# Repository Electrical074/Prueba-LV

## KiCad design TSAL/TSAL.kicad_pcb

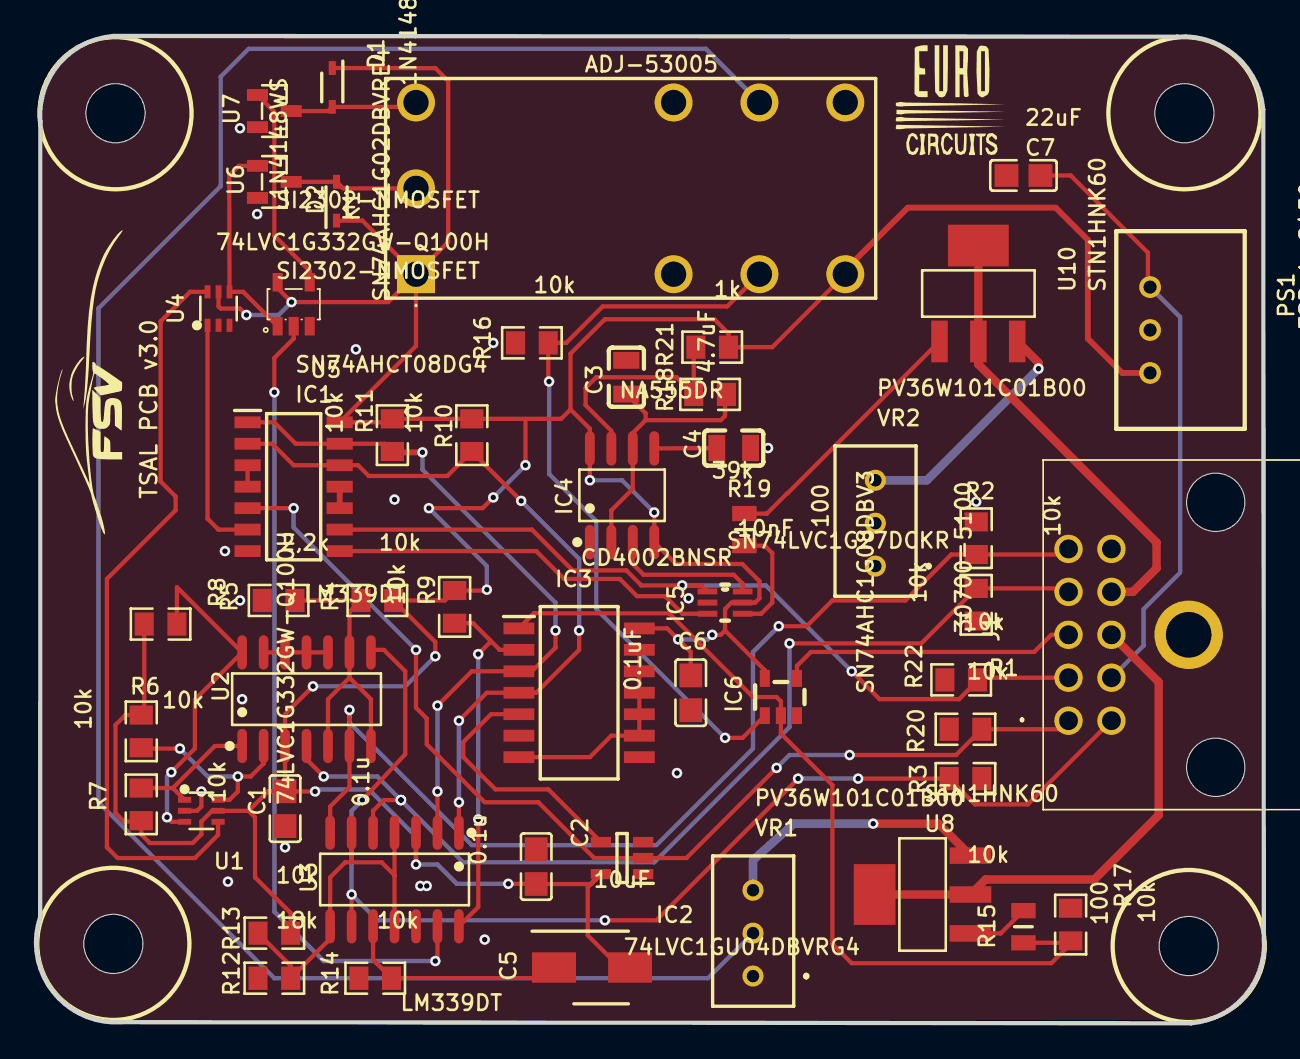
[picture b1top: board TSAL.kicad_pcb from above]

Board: 2 copper layers, 72.7 x 58.4 mm, 55 parts (0 on the bottom side), 43 nets.

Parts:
C1, C2: 0.1u; C0805
C3: 4.7uF; C0805
C4: 10nF; C0805
C5: 10uF; CAPAE430X610N
C6: 0.1uF; C0805
C7: 22uF; C0805
D1, D2: 1N4148WS; SODFL2512X90N
Hole_gge13843: Hole_gge13843
Hole_gge14353: Hole_gge14353
Hole_gge14599: Hole_gge14599
Hole_gge17936: Hole_gge17936
IC1: SN74AHCT08DG4; SOIC127P600X175-14N
IC2: 74LVC1GU04DBVRG4; SOT95P280X145-5N
IC3: CD4002BNSR; SOIC127P780X200-14N
IC4: NA555DR; SOIC-8_L4.9-W3.9-P1.27-LS6.0-BL
IC5: SN74LVC1G27DCKR; SOT65P210X110-6N
IC6: SN74AHC1G08DBV3; SOT-23-5_L2.9-W1.6-P0.95-LS2.8-BR
J1: 30700-5100; 307005100
K1: ADJ-53005; ADJ54005
PS1: TSR_1-2450; TSR-1-24120
R1, R2, R3, R4, R6, R7, R8, R9, R10, R11, R13, R14, R16, R17, R20, R22: 10k; R0805_NEW
R5: 2,2k; R0805_NEW
R12: 18k; R0805_NEW
R15, R19: 100; RESC2012X60N
R18: 39k; R0805_NEW
R21: 1k; R0805_NEW
U1, U4: 74LVC1G332GW-Q100H; SOT-363_L2.0-W1.3-P0.65-LS2.1-BL
U2, U3: LM339DT; SOIC-14_L8.7-W3.9-P1.27-LS6.0-BL
U5: SN74AHC1G02DBVRE4; SOT-23-5_L3.0-W1.7-P0.95-LS2.8-BR
U6, U7: SI2302-NMOSFET; SOT-23-3_L2.9-W1.3-P1.90-LS2.4-BR
U8, U10: STN1HNK60; SOT-223-4_L6.5-W3.5-P2.30-LS7.0-BR
VR1, VR2: PV36W101C01B00; PV36W201C01B00

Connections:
0.9V: R4.1, R5.2, U2.5, U2.7, U2.9
3.2V: R12.2, R13.1, U3.4, U3.6, U3.8, U3.11
+5V: C1.1, C2.1, C5.2, C6.2, D1.1, D2.1, IC1.14, IC2.5, IC3.14, IC4.4, IC4.8, IC5.5, IC6.5, K1.1, K1.4, PS1.3, R4.2, R6.2, R7.2, R8.2, R9.2, R10.2, R11.2, R13.2, R21.2, U1.5, U2.3, U3.3, U4.5, U5.5
ACCU_VOLTAGE_FAULT: IC1.6, U4.1
AIR+: J1.4, R1.2, U2.4, U3.5
AIR+_STATE: IC1.1, IC1.13, IC3.3, R11.1, U3.2
AIR-: J1.5, R2.2, U2.6, U3.7
AIR-_STATE: IC1.2, IC1.12, IC3.4, R10.1, U3.1
DC_LINK_VOLTAGE_FAULT: IC1.8, IC5.3
FAULT_SIGNAL: U4.4, U5.1, U6.1
GND: C1.2, C2.2, C3.1, C4.1, C6.1, C7.1, IC1.7, IC2.3, IC3.7, IC3.9, IC3.10, IC3.11, IC3.12, IC3.13, IC4.1, IC5.2, IC6.3, J1.10, K1.5, PS1.2, R1.1, R2.1, R3.1, R5.1, R12.1, R14.1, R16.1, R17.1, R20.1, R22.1, U1.2, U2.10, U2.11, U2.12, U2.13, U3.12, U4.2, U4.3, U5.3, U6.2, U7.2, VR2.2
G_LED_ACTIVATION: IC3.1, IC6.2, R15.2, R17.2
G_LED_ENABLE: K1.6, VR1.2
IC1_3: IC1.3, IC1.4
IC1_11: IC1.10, IC1.11
IC2_4: IC2.4, IC3.5
IC4_2: C3.2, IC4.2, IC4.6, R18.1
IC4_5: C4.2, IC4.5
IC4_7: IC4.7, R18.2, R21.1
INT_SIGNAL: IC6.1, K1.3, R16.2
K1_8: D1.2, K1.8, U7.3
K1_9: D2.2, K1.9, U6.3
LATCH: U3.13, U5.2
OSCILLATOR: IC4.3, IC5.6
PRECH-RELAY: J1.6, R3.2, U2.8, U3.9
P_RELAY_STATE: IC3.2, R9.1, U3.14
R15_1: R15.1, U8.1
R19_1: R19.1, U10.1
RELAY_FAULT: U1.4, U4.6
R_LED_ACTIVATION: IC5.4, R19.2
TSAL_G_GND: J1.8, U8.2, U8.4
TSAL_R_GND: J1.9, U10.2, U10.4
TS_ACTIVE_ACCU: IC1.5, IC2.2, J1.1, R20.2
TS_ACTIVE_DC_LINK: IC1.9, IC5.1, J1.2, R22.2
TS_STATE: IC6.4, J1.3
U2_1: R7.1, U1.1, U2.1
U2_2: R6.1, U1.6, U2.2
U2_14: R8.1, U1.3, U2.14
U3_10: C5.1, R14.2, U3.10
U5_4: U5.4, U7.1
U8_3: U8.3, VR1.3
U10_3: U10.3, VR2.3
VCC: C7.2, J1.7, PS1.1

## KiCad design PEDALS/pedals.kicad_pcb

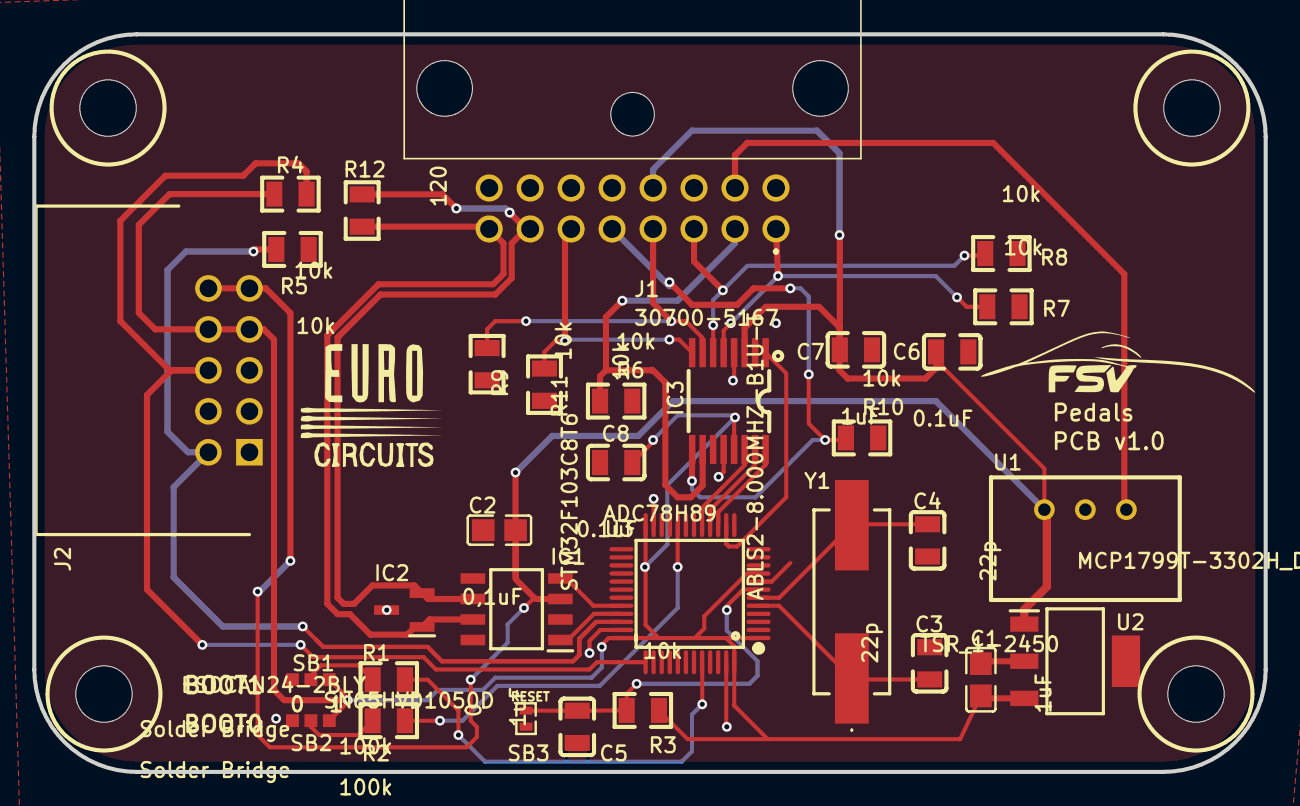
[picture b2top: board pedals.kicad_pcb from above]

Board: 2 copper layers, 76.3 x 45.7 mm, 36 parts (0 on the bottom side), 27 nets.

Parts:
C1, C5, C7: 1uF; C0805
C2: 0,1uF; C0805
C3, C4: 22p; C0805
C6, C8: 0.1uF; C0805
Hole_gge27180: Hole_gge27180
Hole_gge27183: Hole_gge27183
Hole_gge27186: Hole_gge27186
Hole_gge27189: Hole_gge27189
IC1: SN65HVD1050D; SOIC127P600X175-8N
IC2: ESDCAN24-2BLY; SOT105P255X150-3N
IC3: ADC78H89; TSSOP-16_L5.0-W4.4-P0.65-LS6.4-BL
J1: 30700-5167; 307005167
J2: 61201021721; SHDRRA10W64P254X254_2X5_2036X8
R1, R2: 100k; R0805
R3, R4, R5, R6, R7, R8, R9, R10, R11: 10k; R0805
R12: 120; R0805
SB1, SB2: Solder Bridge; SOLDER BRDIGE
SB3: 0; R0402
U1: TSR_1-2450; TSR-1-24120
U2: MCP1799T-3302H_DB; SOT230P700X180-4N
U3: STM32F103C8T6; LQFP-48_L7.0-W7.0-P0.50-LS9.0-BL
Y1: ABLS2-8.000MHZ-B1U-T; ABLS

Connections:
3V3: C1.2, C8.1, IC3.13, J2.7, J2.8, R3.2, R4.2, SB1.1, SB2.1, U2.3, U3.1, U3.9, U3.24, U3.36, U3.48
+5V: C2.1, C6.2, C7.2, IC1.3, IC3.3, J1.12, J2.9, J2.10, U1.3, U2.1
+24V: J1.10, U1.1
BOOT0: R1.1, U3.44
BOOT1: R2.1, U3.20
CAN_H: IC1.7, IC2.1, J1.8, R12.2
CAN_L: IC1.6, IC2.2, J1.7, R12.1
CAN_RX: IC1.4, U3.32
CAN_TX: IC1.1, U3.33
GND: C1.1, C2.2, C3.2, C4.2, C5.1, C6.1, C7.1, C8.2, IC1.2, IC1.8, IC2.3, IC3.4, IC3.12, J1.13, J1.15, J1.16, J2.3, J2.4, R5.1, R6.2, R7.2, R8.2, R9.2, R10.2, R11.2, SB1.3, SB2.3, SB3.1, U1.2, U2.2, U2.4, U3.8, U3.23, U3.35, U3.47
R1_2: R1.2, SB1.2
R2_2: R2.2, SB2.2
RST: C5.2, R3.1, SB3.2, U3.7
SPI_CS1: IC3.1, U3.14
SPI_MISO: IC3.15, U3.16
SPI_MOSI: IC3.14, U3.17
SPI_SCK: IC3.16, U3.15
SWCLK: J2.6, R4.1, U3.37
SWDIO: J2.2, R5.2, U3.34
VA_1: IC3.6, J1.3, R8.1
VA_2: IC3.5, J1.1, R7.1
VD_1: IC3.8, J1.6, R11.1
VD_2: IC3.7, J1.4, R9.1
VF_1: IC3.9, J1.5, R10.1
VF_2: IC3.10, J1.2, R6.1
Y1_1: C3.1, U3.5, Y1.1
Y1_2: C4.1, U3.6, Y1.2
